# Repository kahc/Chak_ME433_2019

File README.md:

# Chak_ME433_2019
Repo for ME433 Spring '19
for Chak Lee

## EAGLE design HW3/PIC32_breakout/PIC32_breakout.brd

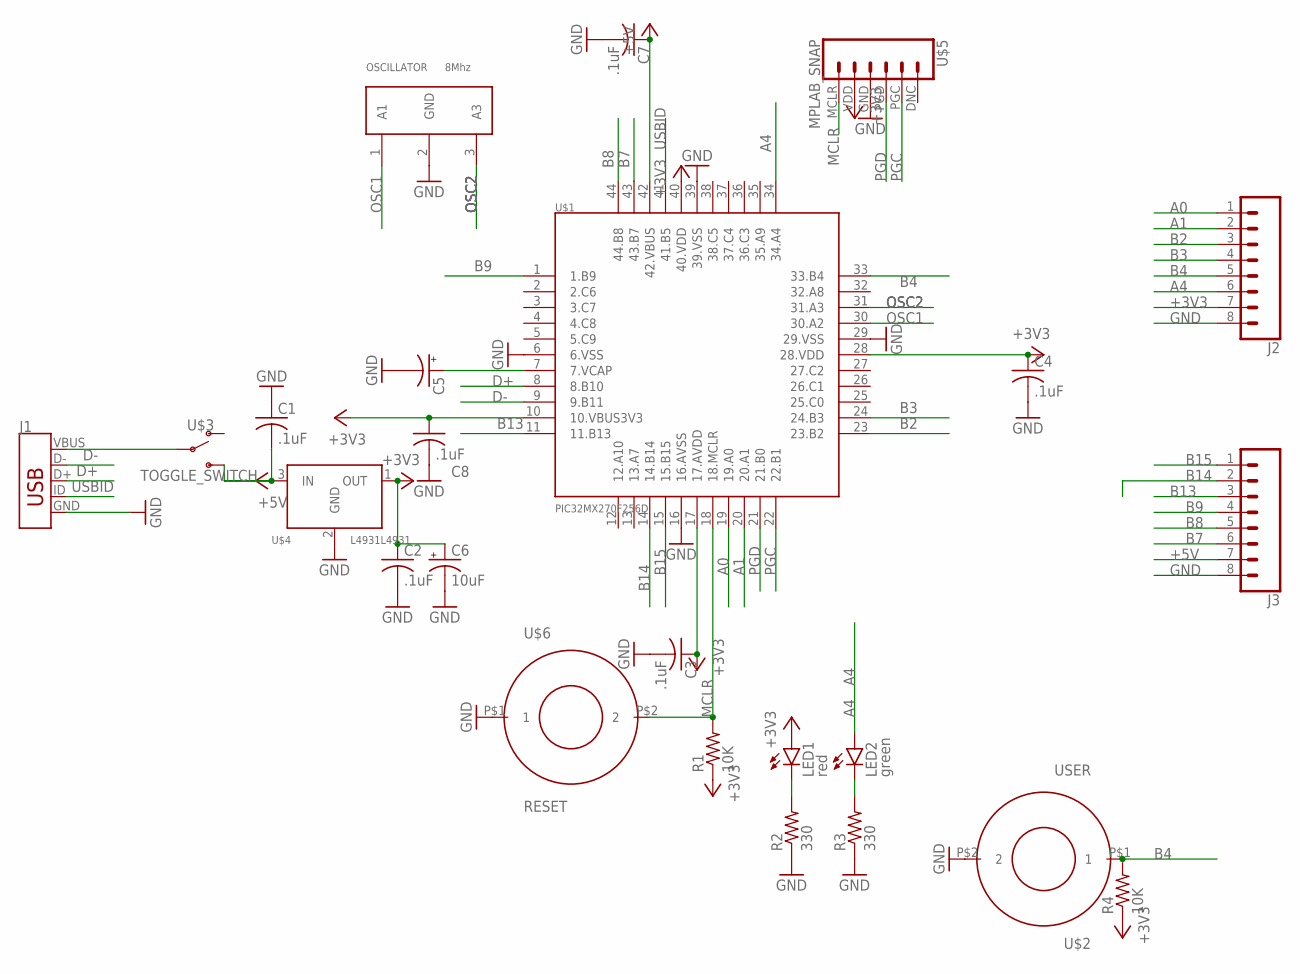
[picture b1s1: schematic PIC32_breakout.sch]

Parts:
C1, C2, C3, C4, C7, C8: .1uF; C025-025X050
C5: CPOL-USB45181B; B45181B
C6: 10uF; B45181B
J1: USB_MICRO-B; AMPHENOL609-4618-1-ND
J2, J3: CONN_08"; 1X08
LED1: red; LED3MM
LED2: green; LED3MM
OSCILLATOR: 8Mhz; 1X03
R1, R4: 10K; 0207/10
R2, R3: 330; 0207/10
U$1: PIC32MX270F256D; TQFP44
U$2: USER; BTN_2
U$3: TOGGLE_SWITCH; TOGGLE
U$4: L4931L4931; TO92
U$5: MPLAB_SNAP; 1X06
U$6: RESET; BTN_2

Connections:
+3V3: C2.1, C3.1, C4.1, C6.+, C8.1, J2.7, LED1.A, R1.1, R4.1, U$1.10 (10.VBUS3V3), U$1.17 (17.AVDD), U$1.28 (28.VDD), U$1.40 (40.VDD), U$4.1 (OUT), U$5.VDD
+5V: C1.2, C7.1, J3.7, U$1.42 (42.VBUS), U$3.P$3 (OUT2), U$4.3 (IN)
A0: J2.1, U$1.19 (19.A0)
A1: J2.2, U$1.20 (20.A1)
A4: J2.6, LED2.A, U$1.34 (34.A4)
B2: J2.3, U$1.23 (23.B2)
B3: J2.4, U$1.24 (24.B3)
B4: J2.5, R4.2, U$1.33 (33.B4), U$2.P$1 (1)
B7: J3.6, U$1.43 (43.B7)
B8: J3.5, U$1.44 (44.B8)
B9: J3.4, U$1.1 (1.B9)
B13: J3.3, U$1.11 (11.B13)
B14: J3.2, U$1.14 (14.B14)
B15: J3.1, U$1.15 (15.B15)
D+: J1.D+, U$1.8 (8.B10)
D-: J1.D-, U$1.9 (9.B11)
GND: C1.1, C2.2, C3.2, C4.2, C5.-, C6.-, C7.2, C8.2, J1.GND, J2.8, J3.8, OSCILLATOR.2 (GND), R2.1, R3.1, U$1.6 (6.VSS), U$1.16 (16.AVSS), U$1.29 (29.VSS), U$1.39 (39.VSS), U$2.P$2 (2), U$4.2 (GND), U$5.GND, U$6.P$1 (1)
MCLR: R1.2, U$1.18 (18.MCLR), U$5.MCLR, U$6.P$2 (2)
unnamed: LED1.K (C), R2.2
unnamed: LED2.K (C), R3.2
unnamed: J1.VBUS, U$3.P$1 (IN)
unnamed: C5.+, U$1.7 (7.VCAP)
OSC1: OSCILLATOR.1 (A1), U$1.30 (30.A2)
OSC2: OSCILLATOR.3 (A3), U$1.31 (31.A3)
PGC: U$1.22 (22.B1), U$5.PGC
PGD: U$1.21 (21.B0), U$5.PGD
USBID: J1.ID, U$1.41 (41.B5)

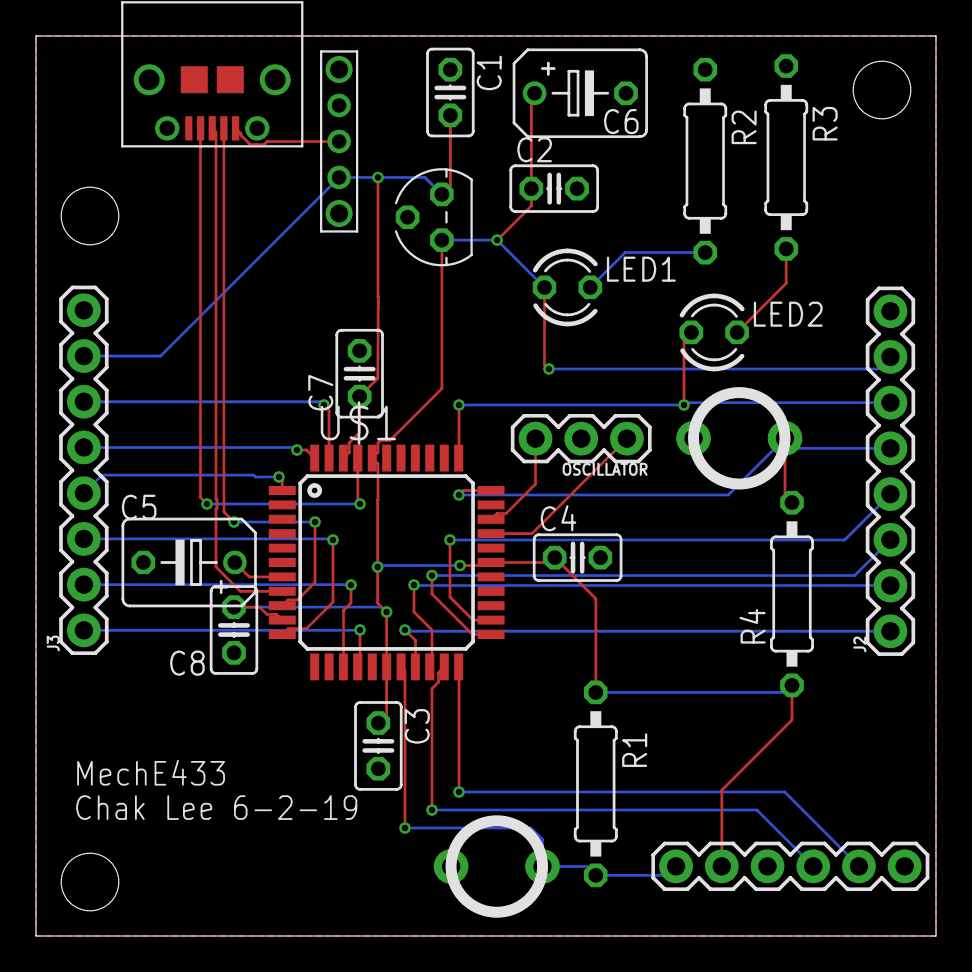
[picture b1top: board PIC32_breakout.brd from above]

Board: 2 copper layers, 50.0 x 50.0 mm, 24 parts (0 on the bottom side), 27 nets.

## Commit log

2019-04-11 added pictures and empty mplab ide project
2019-04-11 added devcfg bits
2019-04-11 saved all files
2019-04-11 added polling clock to code, added two pictures for hw
2019-04-11 got 1kHz square wave working
2019-06-01 added button
    needed to turn off analog input to get digital input
2019-06-01 HW1 finished
    added video
2019-06-02 HW2 finished
    copied over from EAGLE folder.
    microB USB connector is sketchy.
2019-06-02 HW3 finished
    board finished. Should check usb microB just in case
2019-06-02 refactor HW1 code
    added names for pins for better use later
2019-06-03 checked board CAM
    added mounting holes and checked CAM files against Seeed. They let me add to cart so I'll assume it's fine.
2019-06-03 began HW4 project
    cleaned up HW1 code into "PIC_config.h" and "PIC_config.c"
2019-06-03 HW4 setup
    successfully moved pragma configs to a new file so that "main.c" would be clean.
2019-06-03 added useful files
    ty nick
2019-06-03 added declarations
    added more files, more organization, and function declarations.
2019-06-04 SPI working
    got SPI working, added sine and triangle wave generation
2019-06-04 HW4 finished
    added required photos, and final code
2019-06-04 created HW5 folder
    also changed config file to default analog input to off
2019-06-04 organized files for HW5
    added files, copied i2c stuff from class repo, and added necessary function declarations
2019-06-04 changed dac pins
    changed dac pins because they were interfering with i2c pins
2019-06-05 code finished?
    everthing should work, but nothing is working. time to debug
2019-06-05 HW5 finished
    bug was pin numbers start at 0 and not 1. I blame matlab.
2019-06-05 deleted fake branch
2019-06-05 created HW6 project
2019-06-05 Create hw5_demo_low_res.mp4
    full resolution video is stuck in google photos
2019-06-05 LCD started
    got LCD color and pixeldraw working, confired hardware is okay
2019-06-05 HW6 progress
    LCD_drawChar works
2019-06-05 added LCD_drawLine
    drawLine can also do bad diagonal lines, but it will be used for the progress bar
2019-06-05 finished HW6
    video coming later.
2019-06-05 created HW7
    also added LCD_drawRectangle
2019-06-05 HW7 files organizaed
    also added video to HW5 & 6
2019-06-06 read/write problems
    copied over from HW5
2019-06-07 defined accelerometer registers
    for convenience
2019-06-08 added LCD_drawWord
    and theoretically finished the i2c stuff
2019-06-08 basic i2c works
    read who_am_i register
2019-06-08 HW7 finished
    fixed LCD_drawRectangle to draw any rectangles, not just ones where the x2>x1 and y2>y1. Added accelerometer data processing code. Data is collected at 20Hz, and the screen is cleared every 5Hz, to b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
2019-06-08 polishing HW7
    flipped bar direction and added protection against off-screen drawing
2019-06-09 HW8 created
    got HW1 working with harmony
2019-06-09 HW8 completed
    copied over the code and it worked
2019-06-09 HW9 created
    copied HW7 exactly
2019-06-09 HW7 functions written
    time to debug
2019-06-09 got touchscreen working
    was electrical error
2019-06-09 map touchscreen to coordinates
2019-06-09 got buttons working
    but works on press, not release
2019-06-09 HW9 finished
    got button working
2019-06-09 added video for HW7
    preparing to turn in HW7 & 8
2019-06-09 HW10 folder created
    got initial USB communication
2019-06-11 HW10 finished
    bug was forgetting to turn off analog inputs, again.
2019-06-11 started HW11
    successfully copied HW10 over to HW11 folder
2019-06-11 got communication
    format as csv and put into excel
2019-06-11 got matlab and MAF
    got matlab connected, and implemented MAF. If you take multiple readings, MAF buffer is not cleared, but that's probably okay
2019-06-11 HW11 finished
    implemented IIR and FIR
2019-06-11 added Matlab files
    edited from ME333
2019-06-12 created HW12 folder
    will not work with computer?
2019-06-12 HW13 started
    wheels done
2019-06-12 HW13 and HW14 finished
    pictures coming soon
2019-06-12 created motor mount
2019-06-12 added pictures for HW13 and 14
    finished up CAD for HW16 as well
2019-06-12 HW14 finished
    moved it to HW14 folder
2019-06-13 started HW15
    got interrupt triggering
2019-06-13 got blinking
    ISR works at the right speed
2019-06-13 got PWM working
2019-06-13 HW15 finished
    got the plotting function. Used motors intead of LED, which should be okay
2019-06-13 HW16 progress
    it moves, but camera is too slow. Bad solution? move slower
2019-06-13 HW16 finished
    camera is too slow, so only move wheels for a fraction of a second after image received. Also, slow down in corners.
2019-06-14 added videos
    for 15 and 16
